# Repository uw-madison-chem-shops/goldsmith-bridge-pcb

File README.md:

# Goldsmith Bridge PCB 

A very boring PCB used by the Goldsmith Group as a sample holder.

PCB images generated with [tracespace](https://github.com/tracespace/tracespace) follow.

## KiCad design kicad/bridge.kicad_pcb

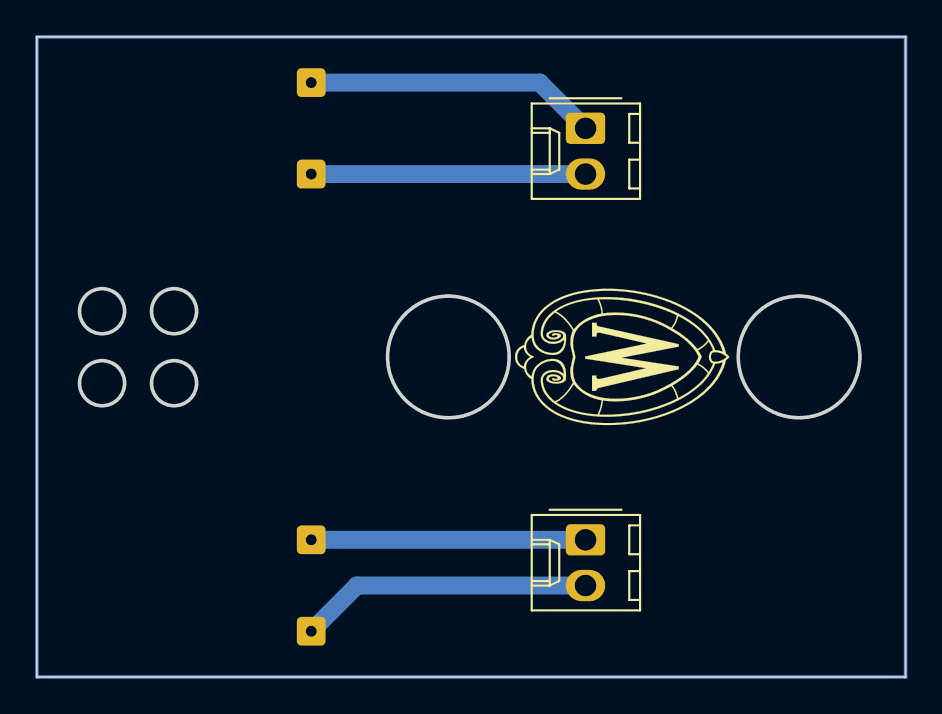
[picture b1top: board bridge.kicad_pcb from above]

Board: 2 copper layers, 48.3 x 35.6 mm, 6 parts (0 on the bottom side), 4 nets.

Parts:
J1, J2, J5, J6: Conn_01x01; SolderWire-0.1sqmm_1x01_D0.4mm_OD1mm
J3, J4: Conn_01x02; Molex_KK-254_AE-6410-02A_1x02_P2.54mm_Vertical

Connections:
unnamed: J3.1, J5.1
unnamed: J3.2, J6.1
unnamed: J1.1, J4.1
unnamed: J2.1, J4.2

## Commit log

2023-11-28 gerbers
